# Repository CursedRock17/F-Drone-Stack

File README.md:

# Welcome to the F-Drone-Stack

## Introduction
This is project for the [MATRIX Lab](https://matrix.umd.edu/) at the University of Maryland's SMART
building. It utilizes dRehmFlight (by nickrehm) as a flight controller.

The intent of the project is to create a stack for replicable, autonmous
drones. These drones utilize a soft-core ARM Cortex M3 on an FPGA to
allow the software to not be restricted to any certain chip which can
be used on quadrotors of any size or scale.

Clone this repository with the version you'd like: `git clone https://github.com/CursedRock17/F-Drone-Stack.git -b humble`

## Software Setup
--------------------------------------------
### Required External Resources (Libraries)
 - Vivavdo [Download](https://www.amd.com/en/products/software/adaptive-socs-and-fpgas/vivado/vivado-buy.html)
 - ARM [Cortex M3](https://developer.arm.com/documentation/101483/0000/introduction/directory-structure) replicable architecture for Artix A7 FPGA

### CRSF Protocol Overview
 - CRSF Telemetry [PX4 Guide](https://docs.px4.io/main/en/telemetry/crsf_telemetry.html)
 - Telemtry [Messages](https://docs.px4.io/main/en/telemetry/crsf_telemetry.html#telemetry-messages)

<details>
<summary> Arduino Setup Steps </summary>

Prerequiste Installs

1. Install [Arduino](https://www.arduino.cc/en/software/) for your respective system
2. Install the [Teensyduino](https://www.pjrc.com/teensy/td_download.html) add-on for your respective system
   : *Note* Make sure you're using versino 1.57.3.
3. Install the [CRSFforArduino](https://github.com/ZZ-Cat/CRSFforArduino) library
4. Navigate to the directory in which you cloned the repo: `cd ~/user/F-Drone-Stack`
5. You have successfully installed the software stack!

</details>

<details>
<summary> Vivado Setup Steps </summary>

** Be Warned Vivado is a **FAT** install **
1. Install [Vivado](https://www.xilinx.com/support/download/index.html/content/xilinx/en/downloadNav/vivado-design-tools.html) for your OS
    1. For Linux: Download the `.bin` file, open up a terminal, `cd ~/Downloads`
    2. Make the file installable: `chmod +x <installer_name>.bin`
    3. Run install: `sudo <installer_name>.bin`
2. Go through the setup manager, you only need the free version for this project
    1. In Detail: Sign-in with your AMD account
    2. Install Vivado ML Standard
    3. In Devices, add "7-Series > Artix-7 FPGAs"
    4. Agree to all the licenses, scrolling to the bottom
    5. Install in the "/tools/Xilinx" directory, or wherever's best for you
    6. Cry as you watch your RAM wither away
        1. If you're on Linux, install the cable drivers, so we can program it: `cd /tools/Xilinx/data/xicom/cable_drivers/lin64/install_script/install_drivers`
        2. Make sure you're added, sudo adduser $USER dialout
    7. Source the install: "source /tools/Xilinx/<version>/settings64.sh"
    8. Run the program, (Linux): `vivado` (Windows): double click app
3. Install the [ARM Cortex IP](https://developer.arm.com/documentation/101483/0000/?lang=en)
    1. See if you're respective university/company already has it (UMD does!), if not apply for the [DesignStart program](https://www.arm.com/resources/program-reg/flexible-access-designstart-tier)
    2. Once you gain access go to [ARM Developer's Product Hub](https://developer.arm.com/downloads/)
    3. Go to [DesignStart Physical IP](https://developer.arm.com/downloads/search?programme=DesignStart&term=Cortex-M3+Processor&entitled=false) and grab the `Cortex M3`
4. Boot up Vivado, we can do so by sourcing the shell script:

</details>

### Running the Software
1. Open the Arduino IDE
2. We now need to open the correct version of the software to make adjustments: In the top left corner of the IDE go to “File > Open > ~/user/F-Drone-Stack/dRehmFlight/Versions/dRehmFlight_Teensy_BETA_1.3”
3. We now need to select the correct board, which in our case is the Teensy 4.1 (but 4.0 works just fine). Go to “Tools > Board > Teensy > Teensy 4.1”. Make sure CPU speed is “600 mHz” and USB type is “Serial”
4. At this point in time acquire a data transfer USB and plug it into the Teensy. We can hit “Sketch > Upload” and the board should flash the Arduino file
    1. Note an error I came across was not having the rules for the Teensy board already installed. So if you come across this error do the following:
    2. Open up a terminal window and go to the rules directory, on Linux: “cd /etc/udev/rules.d” or make the directory if it doesn’t exist “mkdir -p /etc/udev/rules.d”
    3. We need to add the Teensy Rules File, now “touch 00-teensy.rules”
    4. In the text editor of your choice, copy the entire file linked above and paste it into the file. Reflash dRehmFlight and the upload should complete
5. Enjoy!

### Flight Computer Setup Steps (Intelligence Stack)

Provides to sort of intelligence like waypoint provision, pose estimation,
and path planning access.

[In Flight Computer Section](./FlightComputer).

### Hardware Setup

[In Hardware Section](./Hardware), steps to find needed parts, assemble,
and troubleshoot the mechanical and electrical parts to a sample drone

You can also find any CAD Files and eCAD files pertaining to the drone

### Handset Setup 

While this code will work autonomously, it's a good idea as always to 
allow manual control via a human pilot, for the testing I used to the 
[Radiomaster Zorro](https://radiomasterrc.com/collections/zorro-radio-control-series/products/zorro-radio-controller).
We will flashing everything through UART and over Wifi.

1) Download the [ExpressLRS Configurator](https://github.com/ExpressLRS/ExpressLRS-Configurator/releases/)
it will make it easier to bind the Handset (Tx) to the ELRS Receiver (Rx)
2) You can plug your Teensy into a computer to get 5V passing through the receiver 
Once it is on, open that Configurator application. There will some options:
  - Releases : Whatever version you installed 
  - Device Category : BETAFPV 2.4 GHz 
  - Device : BETAFPV 2400 RX Lite 
  - Flashing Method : UART
Now, hit `Build and Flash`, it might take a couple minutes.
3) We can now flash the receiver over wifi, download the [ELRS Firmware](https://support.betafpv.com/hc/en-us/articles/24408930358169-Firmware-for-ELRS-Lite-Receiver-2-4GHz)
before you actually flash, since you'll lose access to the internet. 
After waiting about 30 secs there should be a new wifi network:
`ExpressLRS RX` with the password "expresslrs". Join it! 
4) It will automatically put you in the browser so that you can acccss 
the `Firmware Update` section, *Select* the firmware you just downloaded.
Now I had some trouble here where it would tell me there's a mismatch and kick me
out, this happened a couple of times, just repeat it 3-4 times and it will download for you.
5) We can now pair the handset, in the Zorro `Hardware` section (Page 6 in SYS) 
there's a subgroup : `Bind Configuration`, use the right scroll wheel, then press in
6) We will now do the same wifi style setup but with the TX instead.
7) Congrats the two items should be paired!

After you've paired the two together we should tune our controller for the drone.

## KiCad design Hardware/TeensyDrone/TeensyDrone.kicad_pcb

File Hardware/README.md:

# Hardware Section and Setup

Welcome to the mechanical and electrical parts section of the project,
here you can find the entire process of building a custom drone.

### Parts List

#### Electrical Components

| Item             | Part                    | Datasheet                                             | Link                                                                                                                                                                                                   |
|------------------|------------------------:| -----------------------------------------------------:| ------------------------------------------------------------------------------------------------------------------------------------------------------------------------------------------------------:|
| MCU/FC           | Teensy 4.0              | [Datasheet](https://www.pjrc.com/store/teensy40.html) | [Link](https://www.electromaker.io/shop/product/teensy-40?gad_source=1&gad_campaignid=17338710367&gclid=CjwKCAjw4K3DBhBqEiwAYtG_9AoOmjvFSXFEkkdpQb7JbPI9Wz47hlxhBNEYIXRS0C-5BRerjckGFBoCwNUQAvD_BwE)
| IMU              | HiLetgo GY-521          | [Datasheet](https://mm.digikey.com/Volume0/opasdata/d220001/medias/docus/2204/SEN0142_Web.pdf?_gl=1*w6n5j7*_up*MQ..*_gs*MQ..&gclid=Cj0KCQjwuvrBBhDcARIsAKRrkjcRADOJV8dn-wtU01sinVUfGwrihMSZQWBl3n9ofJSYGxhJTd8fDG4aAldAEALw_wcB&gclsrc=aw.ds) | [Link](https://www.amazon.com/HiLetgo-MPU-6050-Accelerometer-Gyroscope-Converter/dp/B078SS8NQV)
| Radio Rx         | ELRS Lite RX 2.4 GHz    | [Datasheet](https://support.betafpv.com/hc/en-us/articles/4402596816409-Manual-for-Nano-Receiver) | [Link](https://betafpv.com/products/elrs-lite-receiver?variant=39582961664134)
| ESC (4in1)       | Mamba F30 Mini          | [Datasheet](https://cdn.shopifycdn.net/s/files/1/0027/2708/4144/files/MK4_F405_MINI_ICM42688P.jpg?v=1658891020) | [Link](https://speedyfpv.com/products/diatone-mamba-f30mini-2-5s-30a-brushless-4-in-1-esc-blheli_s-dshot600?variant=43539432702166&country=US&currency=USD&utm_medium=product_sync&utm_source=google&utm_content=sag_organic&utm_campaign=sag_organic&gad_source=1&gad_campaignid=21376024065&gclid=Cj0KCQjw1JjDBhDjARIsABlM2Ss1GEUBidOX0kPm21NHFVc2s-RZn4kGX1sH1SGZCS8viviWAjkMLesaAoZAEALw_wcB)
| BEC (5V)         | MP1584EN Mini           | [Datasheet](https://www.makerfabs.com/desfile/files/MP1584.pdf) | [Link](https://www.amazon.com/MP1584EN-DC-DC-Converter-Adjustable-Module/dp/B01MQGMOKI)
| Battery (2S)     | GNB Li-ion 2S           | None                                                            | [Link](https://www.gaoneng.shop/products/gaoneng-gnb-2s-7.4v-3000mah-10c-xt60-li-ion-battery-made-with-sony-18650-vtc6)
| Motors (x4)      | HGLRC 11000KV Brushless | [Datasheet](https://www.hglrc.com/products/specter-1202-5-11000kv-brushless-motor?srsltid=AfmBOoqW-ta1qVEoeQz9RS-2Xiud78sCV2YQTAbIZQbJYDzdP6lwds6F) | [Link](https://www.hglrc.com/products/specter-1202-5-11000kv-brushless-motor?srsltid=AfmBOoqW-ta1qVEoeQz9RS-2Xiud78sCV2YQTAbIZQbJYDzdP6lwds6F)
| Optical Flow     | Matek 3901-L0X          | [Datasheet](https://www.mateksys.com/?portfolio=3901-l0x#tab-id-2) | [Link](https://www.getfpv.com/mateksys-optical-flow-lidar-sensor-3901-l0x.html?utm_source=google&utm_medium=cpc&utm_campaign=DM+-+NB+-+PMax+-+Shop+-+No-index+-+SM+-+ALL+%7C+Full+Funnel&utm_content=pmax_x&utm_keyword=&utm_matchtype=&campaign_id=20799936859&network=x&device=c&gc_id=20799936859&gad_source=1&gad_campaignid=20796067361&gclid=CjwKCAjwg7PDBhBxEiwAf1CVu5J9NG6OtZcLzF9Gt-jSDHbckIvNjY7H0FQzeP1tNwYG2YqhNJe9JxoCZTMQAvD_BwE)
| Wires            | 28awg Wires + Connectors| [Datasheet](https://www.molex.com/en-us/products/part-detail/151340402?display=pdf)                                                            | [Link](https://www.amazon.com/Keszoox-Pre-Crimped-Compatible-Controller-Connectors/dp/B09F3TQS9V?th=1)
| Capacitor        | 25V 330uF               | None          | [Link](https://www.digikey.com/en/products/detail/rubycon/25YXF330MEFCT810X12.5/9553865?gclsrc=aw.ds&gad_source=1&gad_campaignid=17336967819&gclid=CjwKCAjw1ozEBhAdEiwAn9qbzVpkC7tEQoLxKylyjwLx9Ek22v4CTqct2tGUgR2duNCr6zZ4ja4pIhoCTzIQAvD_BwE)

#### Mechanical Parts

| Item             | Part                    | Datasheet                                             | Link                                                                                                                                                                                                   |
|------------------|------------------------:| -----------------------------------------------------:| ------------------------------------------------------------------------------------------------------------------------------------------------------------------------------------------------------:|
| Drone Frame      | Carbon Fiber Micro UAS  | None                                                            | None
| Screws(x7)       | M2 12mm Metal Screw     | None                                                            | None
| Nuts(x7)         | M2 Metal Nut            | None                                                            | None
| Screws(x2)       | M3 12mm Nylon Screw     | None                                                            | None
| Nuts(x2)         | M3 Nylon Nut            | None                                                            | None
| Custom PCB       | Copper Board            | The PCB in the Hardware Section                                 | [Hardware](TeensyDrone) 
| Battery Mount    | Battery Holder          | None                                                            | None
| Op Flow Mount    | Op Flow Holder          | None                                                            | None
| Legs(x4)         | TPU printed Legs        | Legs in the TeensyCAD section                                   | [TeensyCAD](TeensyCAD)
| JST SH           | 8-Pin Vertical Shrouded | [Datasheet](https://www.jst-mfg.com/product/pdf/eng/eSH.pdf)                                                            | [Link](https://www.digikey.com/en/products/detail/jst-sales-america-inc/BM08B-SRSS-TB/926700)
| MX PicoBlade (x2)| 4-Pin Vertical Picoblade| [Datasheet](https://www.molex.com/en-us/products/part-detail/533980471?display=pdf)                                                            | [Link](https://www.digikey.com/en/products/detail/molex/0533980471/699068?_gl=1*6zaf8a*_up*MQ..*_gs*MQ..&gclid=CjwKCAjw4efDBhATEiwAaDBpbmVd34wrg8y2s5RDRtP2scQ2MDIMdRvgA0yoEv-UR2EZkolO0P8Q8BoCRToQAvD_BwE&gclsrc=aw.ds)
| MX PicoBlade (x4)| 3-Pin Male Connector    | [Datasheet](https://www.molex.com/en-us/products/part-detail/2181100301)                                                            | [Link](www.digikey.com/en/products/detail/molex/2181100301/14309272?utm_source=oemsecrets&utm_medium=aggregator&utm_campaign=buynow)
| Gemfan 3025  (x4)| 2 Blade Propeller       | [Datasheet](https://grabcad.com/library/gemfan-t-3025-1)             | [Link](https://newbeedrone.com/products/gemfan-3025-pc-2-blade-propeller)

### Drone Characteristics
- Drone Weight: 97g
- 2S Li-Ion Battery Weight: 104g 
- Battery Holder Weight: 5g 
- *Total Weight*: 206g
- CG:
- Motor Thrust vs PWM Signal Curve:

### Assembly

1) Grab your drone Frame, electrical components, and turn on your soldering iron
2) Before you do anything, ensure your PCB's PWR/GND doesn't have any shorts
by testing with a multimeter, there should be 1 big GND plane
3) Use helping hands to hold the PCB still, start by soldering pinouts to tracks
    1) Start with the BEC, ensure it's in the correct orientation, arrow points left
    and solder pins 3 & 7, using the PCB editor as a guide. I placed 2 pin
    headers in each section, soldered those into the board, then sniped them flush
    2) Next we solder the Teensy 4.0 going in the clockwise direction, starting
    with Vin (the top right pin), the USB port should face the BEC, skip 4pins,
    then solder pins 21, 20, (skip 2), 17, 16, (skip 6), 3.3V, (skip 4), 9,
    8, 7, 6, (skip 4), 1, 0. You may want to solder header pins in the vertical
    pinouts of the Teensy itself, then solder matching sockets (14 pin) into
    the board itself, for easy removal of the Teensy.
    3) Solder all 4 JST headers, the 8-pin on the left, two 4-pins on the right
    and another 4-pin on the lower on the right
4) Mount the PCB to the drone frame itself, using three M2 (2") screws, they
   should lie underneath the ESC, so taking it off must be done in reverse
5) The next step is soldering 28-awg wire(Or whatever you have) with
   connectors to the components
   There are 4 components which are wired in this way:
     - ESC Motors (3 connectors each, 4 connectors) Goes RBY for colors,
     string and solder those wires to the edge power pads, then we can
     run the other end of the connector into the corresponding motor
     connectors, so they should click into each other (MX Picoblade)
     male -> female and female -> male
     - ESC (8 pin connector, using 6, top left)
     - IMU (4 pin connector, top right)
     - Optical Flow (4 pin connector, middle right)
     - ELRS (4 pin connector, bottom right)
6) *Optional* : Put a layer of Kapton tape on the bottom of the PCB
7) After we've solder all the components onto the board, we can mount things
   Things have to mounted in a weird order so that we save space
    1) Run the 3 mounting screws for the PCB, through the PCB, but not onto the
    frame
    2) Mount the ESC to the PCB using 4 M2 (2") screws with the custom spacers
    on the opposite side of the ESC, finishing with a M2 nut on the other side
    of the board
    3) The other component being mounted to the PCB is the IMU, with two
    3" screws 12mm Nylon screws. Run the screws through the IMU into rubber
    spacers (gummies) which are finished up by some tight fitting nuts on the
    other side of the PCB
    4) Flip the PCB + Drone over, slotting the mounting screws through and as
    always, finish on the otherside with M2 nuts for each of the 3 screws
8) We must now screw in the battery pack, to the bottom with the holder
9) **Before** plugging in your external connectors or the Teensy, you need to
test the BEC, since it's controlled with a potentiometer. **Ensure no component
can be fried by the 7.4V you'll get from the battery**. Do this in a controlled
environment and set up ahead of time, plug in your battery, take a multimeter
and the easy spot to test will be the back of the board where lies the
Teensy's 5V and GND pins, so being careful as to not short the two, put the
meter on each respective side. You should get about 4.95 - 5.15V, if not,
disassemble. Alternatively you could put temporary header pins into the soldered
socket and test that way. If need be, tune that potentiometer
10) After ensuring you won't fry your connectors, plug in the components.
11) You should use Waxed Nylon String or similar, with a clove hitch knot
followed by a square knot, to tie excess table bundles down to the frame
12) Place your props (not too far down) onto your motors, ensure you have
your props in the correct direction for props out. *Tip* : think about how the
air would flow if it made contact with the prop
13) The drone is now assembled!

### Steps Before Flying
There are some steps we should take, after assembling the drone,
before it gets in the air:
1) Ensure no loose connections between motors and onboard connectors, also
ensure there's no other power source, before plugging in the battery
2) Ensure the drone will not be armed before flight whether it's with a handset, some
teleop data, or an autonomous code
3) Grip the drone well and plug in the battery (2S)
4) Ensure the drone can pitch, roll, and yaw by slowly altering values to one side.
Make sure your throttle speed is low enough so it doesn't fly out of your hand. You may
also want to set RPY=0, then manually turn the drone to each of its' sides to see if
it would balance itself out.
5) Disconnect from any tether or hold on the drone, go a clear space with no unwanted
obstacles.
6) Run your process!

### General Board Setup Requirements
- 1.0mm Power/GND width
- 0.5mm Default Clearance
- 0.5mm Default Track Width + Connection Width
- No need for other trace sizes b/c not very intense
- Min Annular Width = 0.5mm
- Min Via Diameter = 1.0mm
- Copper to Hole/Edge Clearance: 0.5mm
- Min Through Hole: 0.25mm
- Hole -> Hole Clearance: 1.0mm

### Considerations for the future
- [ ] Change Header footprints to corresponding connectors
- [ ] FlipFlop the Servo connector so on the board it's 1 -> 1
- [ ] Since we have access to PCBWay, should probably route more concisely
- [ ] Check the spacing for our headers to ensure the physical part fits
- [ ] Check the spacing from connector to other components like ESC conn. to BEC
- [ ] Reverse order pins for IMU since not enough space
- [ ] Smaller Pitch Surface MNT connectors
- [ ] Enable Clearance for Props (maybe create design of frame and all)
- [ ] Rotate IMU so that it faces front (X points to front)
- [ ] Create a more indepdent, less noisy mount for the correctly rotated IMU (Sticky pads too fragile)
- [ ] Create larger traces for the motors since they drive a lot of current
- [ ] Make the drone colors MD-themed (Red/Black) for legs and frame and maybe props
- [ ] Create a more precise battery mount, mainly for Li-ion battery
- [ ] Make legs a bit wider as Bill said they would stick better
- [ ] Ensure access to Telemetry data from the ESC

### CAD Files
Listed in the directory are the URDF files and JSON config for F-Drone. In order to use 
F-Drone in simulation it needs to be converted to URDF, which should be saved here, but 
if  you update the CAD files, it shouldn't be hard to get those URDFs. 
Instead, we can use `onshape-to-robot`.

<details>
<summary> How to Convert from CAD to URDF (OnShape) </summary>

Prerequiste Installs
- Install onshape-to-robot through `pip install onshape-to-robot`
- Install meshlab through `sudo apt-get install meshlab` (Or whatever your system is)
- Install openscad through `sudo apt-get install openscad` (Or whatever your system is)

1. You need to generate some keys to your OnShape account - navigate to the 
[API Keys](https://cad.onshape.com/appstore/dev-portal/apiKeys) section of OnShape.
2. Click 'Create a new API key' in the top right corner, enable all of the permissions
3. **Wait** you wil provided will a access key and secret key, we need to save them.
4. Open a terminal instance and navigate to the `Hardware` section of the project.
5. Create a script to rerun: `touch onshape.bash`, paste in the following
```
# Access Our CAD files
export ONSHAPE_API=https://cad.onshape.com
export ONSHAPE_ACCESS_KEY=YOUR_ACCESS
export ONSHAPE_SECRET_KEY=YOUR_SECRET
```
You can also use a `.bashrc` or `.env` file if you prefer, then give it run permisions:
`chmod +x onshape.sh` && `source onshape.sh`
6. Run the script, `./onshape.sh` to get those keys 
7. Now anytime you update the CAD file given the document in the `url` section of the 
config.json, you can run `onshape-to-robot ./path-to-config-file` replacing it with your path

</details>

### Key Details to resolve Issues

<details>
<summary> Calibration Sequence Won't Fire </summary>
When in calibration mode, if you don't here the special jingle after arming, one of two things happened.
Either there's not enough "IDLE" time before the calibration due to delays. Or, the range is not
correctly setup for the controller which causes the OneShot125 Protocol to miss the trim
</details>

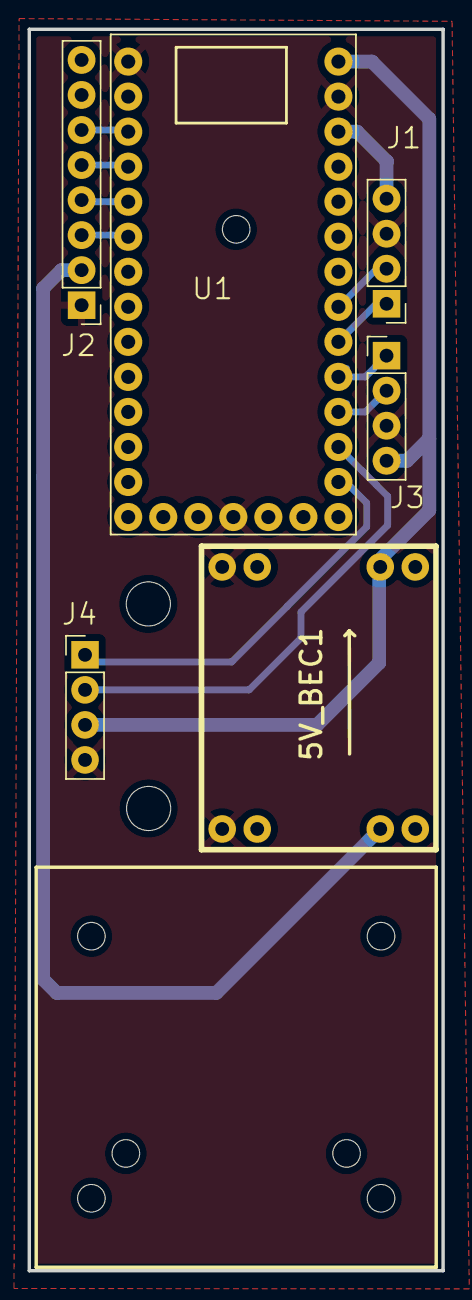
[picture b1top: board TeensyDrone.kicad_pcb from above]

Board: 2 copper layers, 30.0 x 90.0 mm, 15 parts (0 on the bottom side), 14 nets.

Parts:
5V_BEC1: 5V_BEC
H1, H2, H3, H5, H6, H7, H8: MountingHole; MountingHole_2mm
H9, H11: MountingHole; MountingHole_3.2mm_M3
J1, J3, J4: Conn_01x04; PinHeader_1x04_P2.54mm_Vertical
J2: Conn_01x08; PinHeader_1x08_P2.54mm_Vertical
U1: DEV-15583; MODULE_DEV-15583

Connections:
5V: 5V_BEC1.7 (5V), J3.4 (5V), J4.3 (SCL), U1.VIN
+3.3V: J1.4 (SDA), U1.3.3V (3.3)
ELRS_RX: J4.1 (3.3V), U1.14
ELRS_TX: J4.2 (GND), U1.15
GND: 5V_BEC1.1 (GND), 5V_BEC1.5 (GND), J1.3 (SCL), J2.1, J3.3 (GND), J4.4 (SDA), U1.G1 (GND), U1.G2 (GND), U1.G3 (GND)
IMU_SCL: J1.2 (GND), U1.19
IMU_SDA: J1.1 (3.3V), U1.18
unnamed: J2.3, U1.4
unnamed: J2.4, U1.3
unnamed: J2.5, U1.2
unnamed: J2.6, U1.1
OF_RX: J3.1 (RX), U1.17
OF_TX: J3.2 (TX), U1.16
VBat: 5V_BEC1.3 (VBat), J2.2

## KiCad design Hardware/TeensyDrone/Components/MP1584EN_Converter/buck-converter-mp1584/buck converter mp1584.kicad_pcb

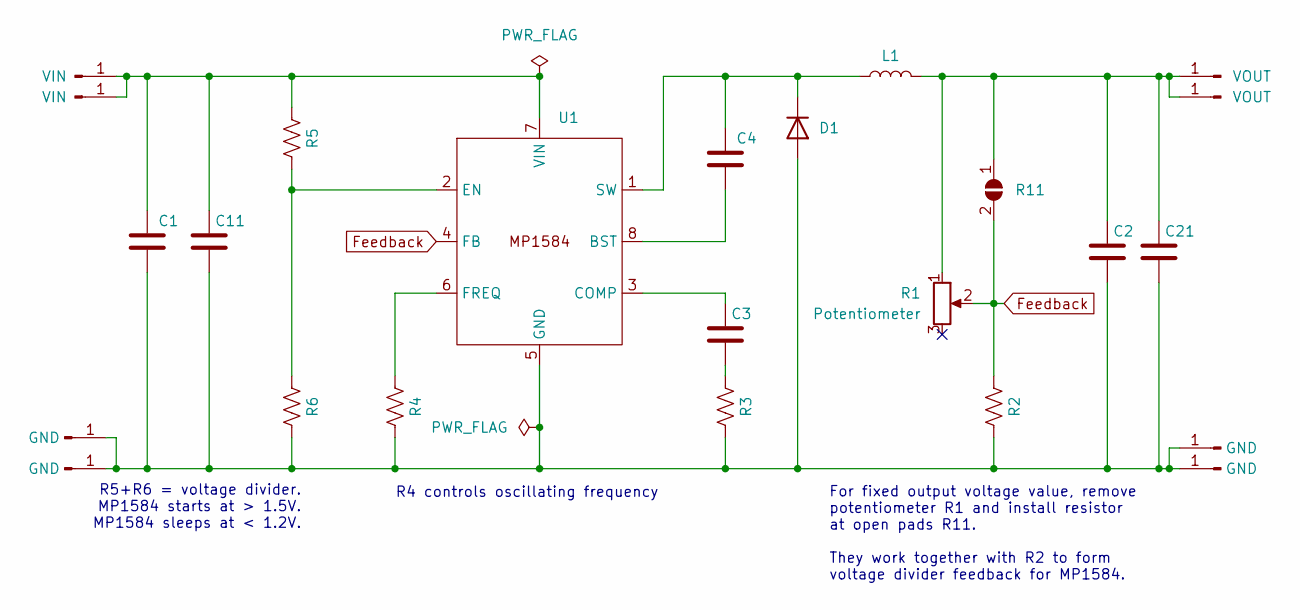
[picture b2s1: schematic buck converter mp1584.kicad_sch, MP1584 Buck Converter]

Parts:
C1, C2: C; C_0805_2012Metric
C3, C4, C11, C21: C; C_0201_0603Metric
D1: D; D_0805_2012Metric
J1, J6: VIN; PinHeader_1x01_P1.00mm_Vertical
J2, J4, J5, J7: GND; PinHeader_1x01_P1.00mm_Vertical
J3, J8: VOUT; PinHeader_1x01_P1.00mm_Vertical
L1: L; L_Neosid_SM-PIC0512H
R1: Potentiometer; Potentiometer_ACP_CA6-H2,5_Horizontal
R2, R3, R4, R5, R6: R_US; R_0201_0603Metric
R11: SolderJumper_2_Open; SolderJumper-2_P1.3mm_Open_Pad1.0x1.5mm
U1: MP1584EN

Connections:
Feedback: R1.2, R2.1, R11.2 (B), U1.4 (FB)
unnamed: C3.2, R3.1
unnamed: C1.2, C2.2, C11.2, C21.2, D1.2 (A), J2.1, J4.1, J5.1, J7.1, R2.2, R3.2, R4.2, R6.2, U1.5 (GND)
unnamed: C4.1, D1.1 (K), L1.1, U1.1 (SW)
unnamed: C1.1, C11.1, J1.1, J6.1, R5.1, U1.7 (VIN)
unnamed: C2.1, C21.1, J3.1, J8.1, L1.2, R1.1, R11.1 (A)
unnamed: C4.2, U1.8 (BST)
unnamed: C3.1, U1.3 (COMP)
unnamed: R5.2, R6.1, U1.2 (EN)
unnamed: R4.1, U1.6 (FREQ)

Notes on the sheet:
R4 controls oscillating frequency
For fixed output voltage value, remove potentiometer R1 and install resistor at open pads R11. They work together with R2 to form voltage divider feedback for MP1584.
R5+R6 = voltage divider. MP1584 starts at > 1.5V. MP1584 sleeps at < 1.2V.

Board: 2 copper layers, 24 parts (0 on the bottom side), 10 nets, no tracks yet.

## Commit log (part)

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2025-06-10 Initial Cutting of Fat
2025-06-10 Fixing Array Bound issues
2025-06-12 Fixing Docs
2025-06-12 Cleaning up Radio Code
2025-06-12 Removing bloat
2025-06-18 Adding Radio (CRSF) Connection
2025-06-26 Adding CRSF
2025-07-03 Uploadinng org original PCB with components
2025-07-03 upload
2025-07-08 Adding Gerbers
2025-07-08 Removing Gerbers
2025-07-11 splitting files
2025-07-17 Moved to Teensy 4.0 from 4.1
2025-07-17 Revert "Moved to Teensy 4.0 from 4.1"
    This reverts commit 64f42becbd12878e856e1dc259d1d069ff850610.
2025-07-17 Revert "splitting files"
    This reverts commit bca84f3fae8bf59e844e86045c33a7267805a79f.
2025-07-17 Revert "Revert "splitting files""
    This reverts commit 3562b8e581463791a03922c4a90183042ac39a13.
2025-07-17 Revert "Revert "Moved to Teensy 4.0 from 4.1""
    This reverts commit 7b94347de4182ec4fe07ca98d08f7a30d7e3d8b2.
2025-07-17 test
2025-07-17 adding module
2025-07-18 Second iteration of PCB
2025-07-20 Teensy 4.0 Iteration 2
2025-07-25 Finished Hardware section
2025-07-25 Done Hardware Section
2025-07-30 Fixing ESCs
2025-07-31 Tracking
2025-07-31 This Works
2025-08-04 Preparring Visualization Code
2025-08-05 Access to Foxglove Acquired
2025-08-05 Temporary Remap
2025-08-06 Adding to TF Visualization with uROS
2025-08-06 Working Code for Flipped Drone
2025-08-08 Moving to Angle Mode
2025-08-10 Adding drone URDF
2025-08-17 Function URDF/SDF Models for RViz/Gazebo
2025-08-20 Adding Technical Review Documents
2025-09-05 Acquired Hardware In the Loop (HIL)
